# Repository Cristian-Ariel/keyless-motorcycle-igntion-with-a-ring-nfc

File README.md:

# Keyless Motorcycle Ignition System with a Ring (NFC)

The purpose of the system is to enable the ignition of a motorcycle without the use of a physical key, by utilizing an NFC tag (Near Field Communication). A few key features of the system include:
- Zero current consumption when the motorcycle is off, preventing battery discharge.
- The ability to store up to 128 different tags in memory, which are used as keys.
- Access to "Modes" such as Save/Delete Tag Mode and Erase All Tags Mode to prevent unauthorized use.
- A modular hardware design for prototyping and upgrades to accommodate different motorcycle makes and models.

## How do I build one?
Please watch the video on [Youtube](https://youtu.be/Ip3jwV7dnoM) or [Odysee](https://odysee.com/@AsyssComplex:1/keyless.motorcycle.ignition.with.ring:4?r=8kbGTNhCZ6iqTXnwzbdhoQCgzBPm1UvK).
Lastly, make sure to read [the documentation](https://drive.google.com/file/d/1D22VbdVqOc0YWlI75PouFQuNAUfmh6G7/view?usp=sharing). There you will find the materials and tools to build the system as well as several sections where we discuss the working principles of the system more in detail. The rest of the files, code, PCB files, 3D files are located in this repository.

## How do I contribute?
In the second page of the documentation, there is a brief description of how you can do it. Since the whole system is an ongoing project, I will edit this page and the description of the videos for future updates. Don't forget that you can also share your thoughts on the comment section of the videos.

## Enjoy!

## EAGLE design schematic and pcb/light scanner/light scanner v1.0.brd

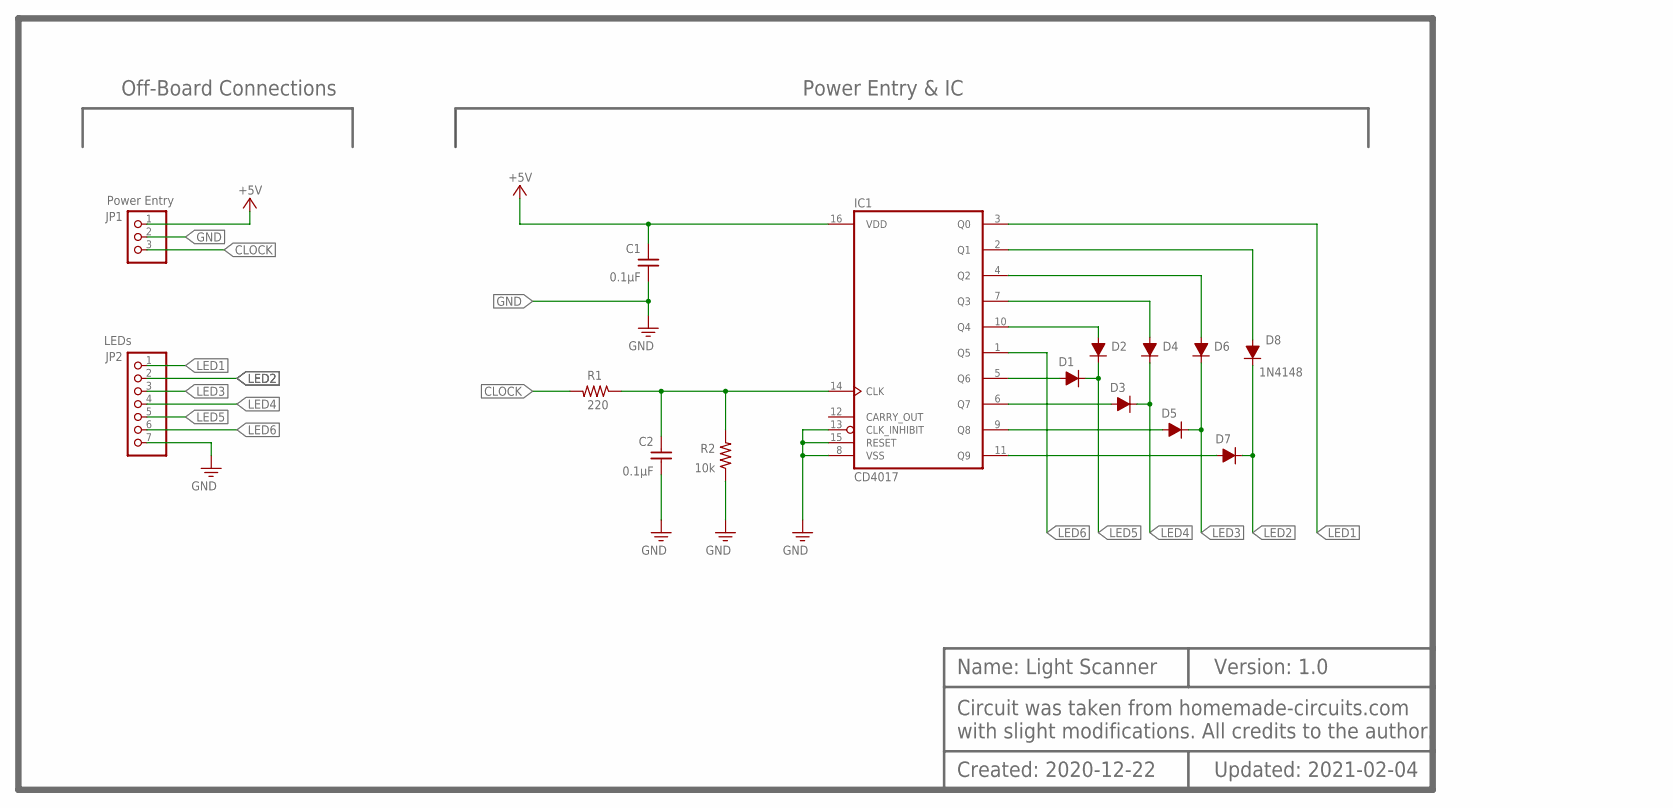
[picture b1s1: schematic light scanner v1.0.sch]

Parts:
C1, C2: 0.1µF; C_H5
D1, D2, D3, D4, D5, D6, D7: D_1N4148; DO35-7A
D8: 1N4148; DO35-7A
IC1: CD4017; DIP16
JP1: Power Entry; 1X03
JP2: LEDs; 1X07
R1: 220; R_THM
R2: 10k; R_THM

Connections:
+5V: C1.1, IC1.16 (VDD), JP1.1
CLOCK: JP1.3, R1.2
GND: C1.2, C2.2, IC1.8 (VSS), IC1.13 (CLK_INHIBIT), IC1.15 (RESET), JP1.2, JP2.7, R2.1
LED1: IC1.3 (Q0), JP2.1
LED2: D7.C, D8.C, JP2.2
LED3: D5.C, D6.C, JP2.3
LED4: D3.C, D4.C, JP2.4
LED5: D1.C, D2.C, JP2.5
LED6: IC1.1 (Q5), JP2.6
unnamed: C2.1, IC1.14 (CLK), R1.1, R2.2
unnamed: D1.A, IC1.5 (Q6)
unnamed: D2.A, IC1.10 (Q4)
unnamed: D3.A, IC1.6 (Q7)
unnamed: D4.A, IC1.7 (Q3)
unnamed: D5.A, IC1.9 (Q8)
unnamed: D6.A, IC1.4 (Q2)
unnamed: D7.A, IC1.11 (Q9)
unnamed: D8.A, IC1.2 (Q1)

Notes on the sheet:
Power Entry & IC
Off-Board Connections
Name: Light Scanner
Circuit was taken from homemade-circuits.com with slight modifications. All credits to the author.
Created: 2020-12-22
Updated: 2021-02-04
Version: 1.0

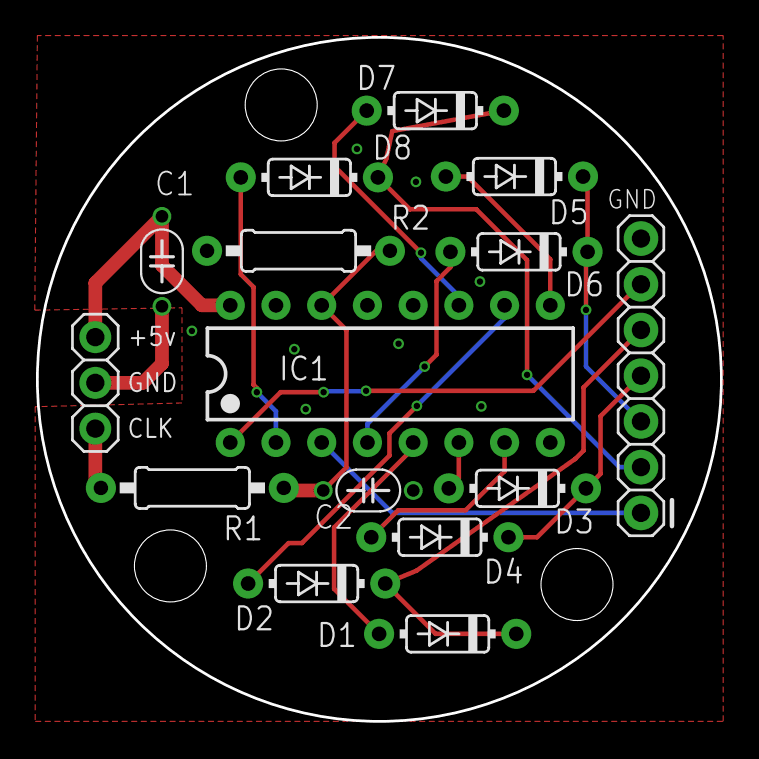
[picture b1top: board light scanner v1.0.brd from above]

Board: 2 copper layers, 38.0 x 38.0 mm, 16 parts (1 on the bottom side), 18 nets.

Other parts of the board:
U$2: ASSYS_COMP_LOGO_V6

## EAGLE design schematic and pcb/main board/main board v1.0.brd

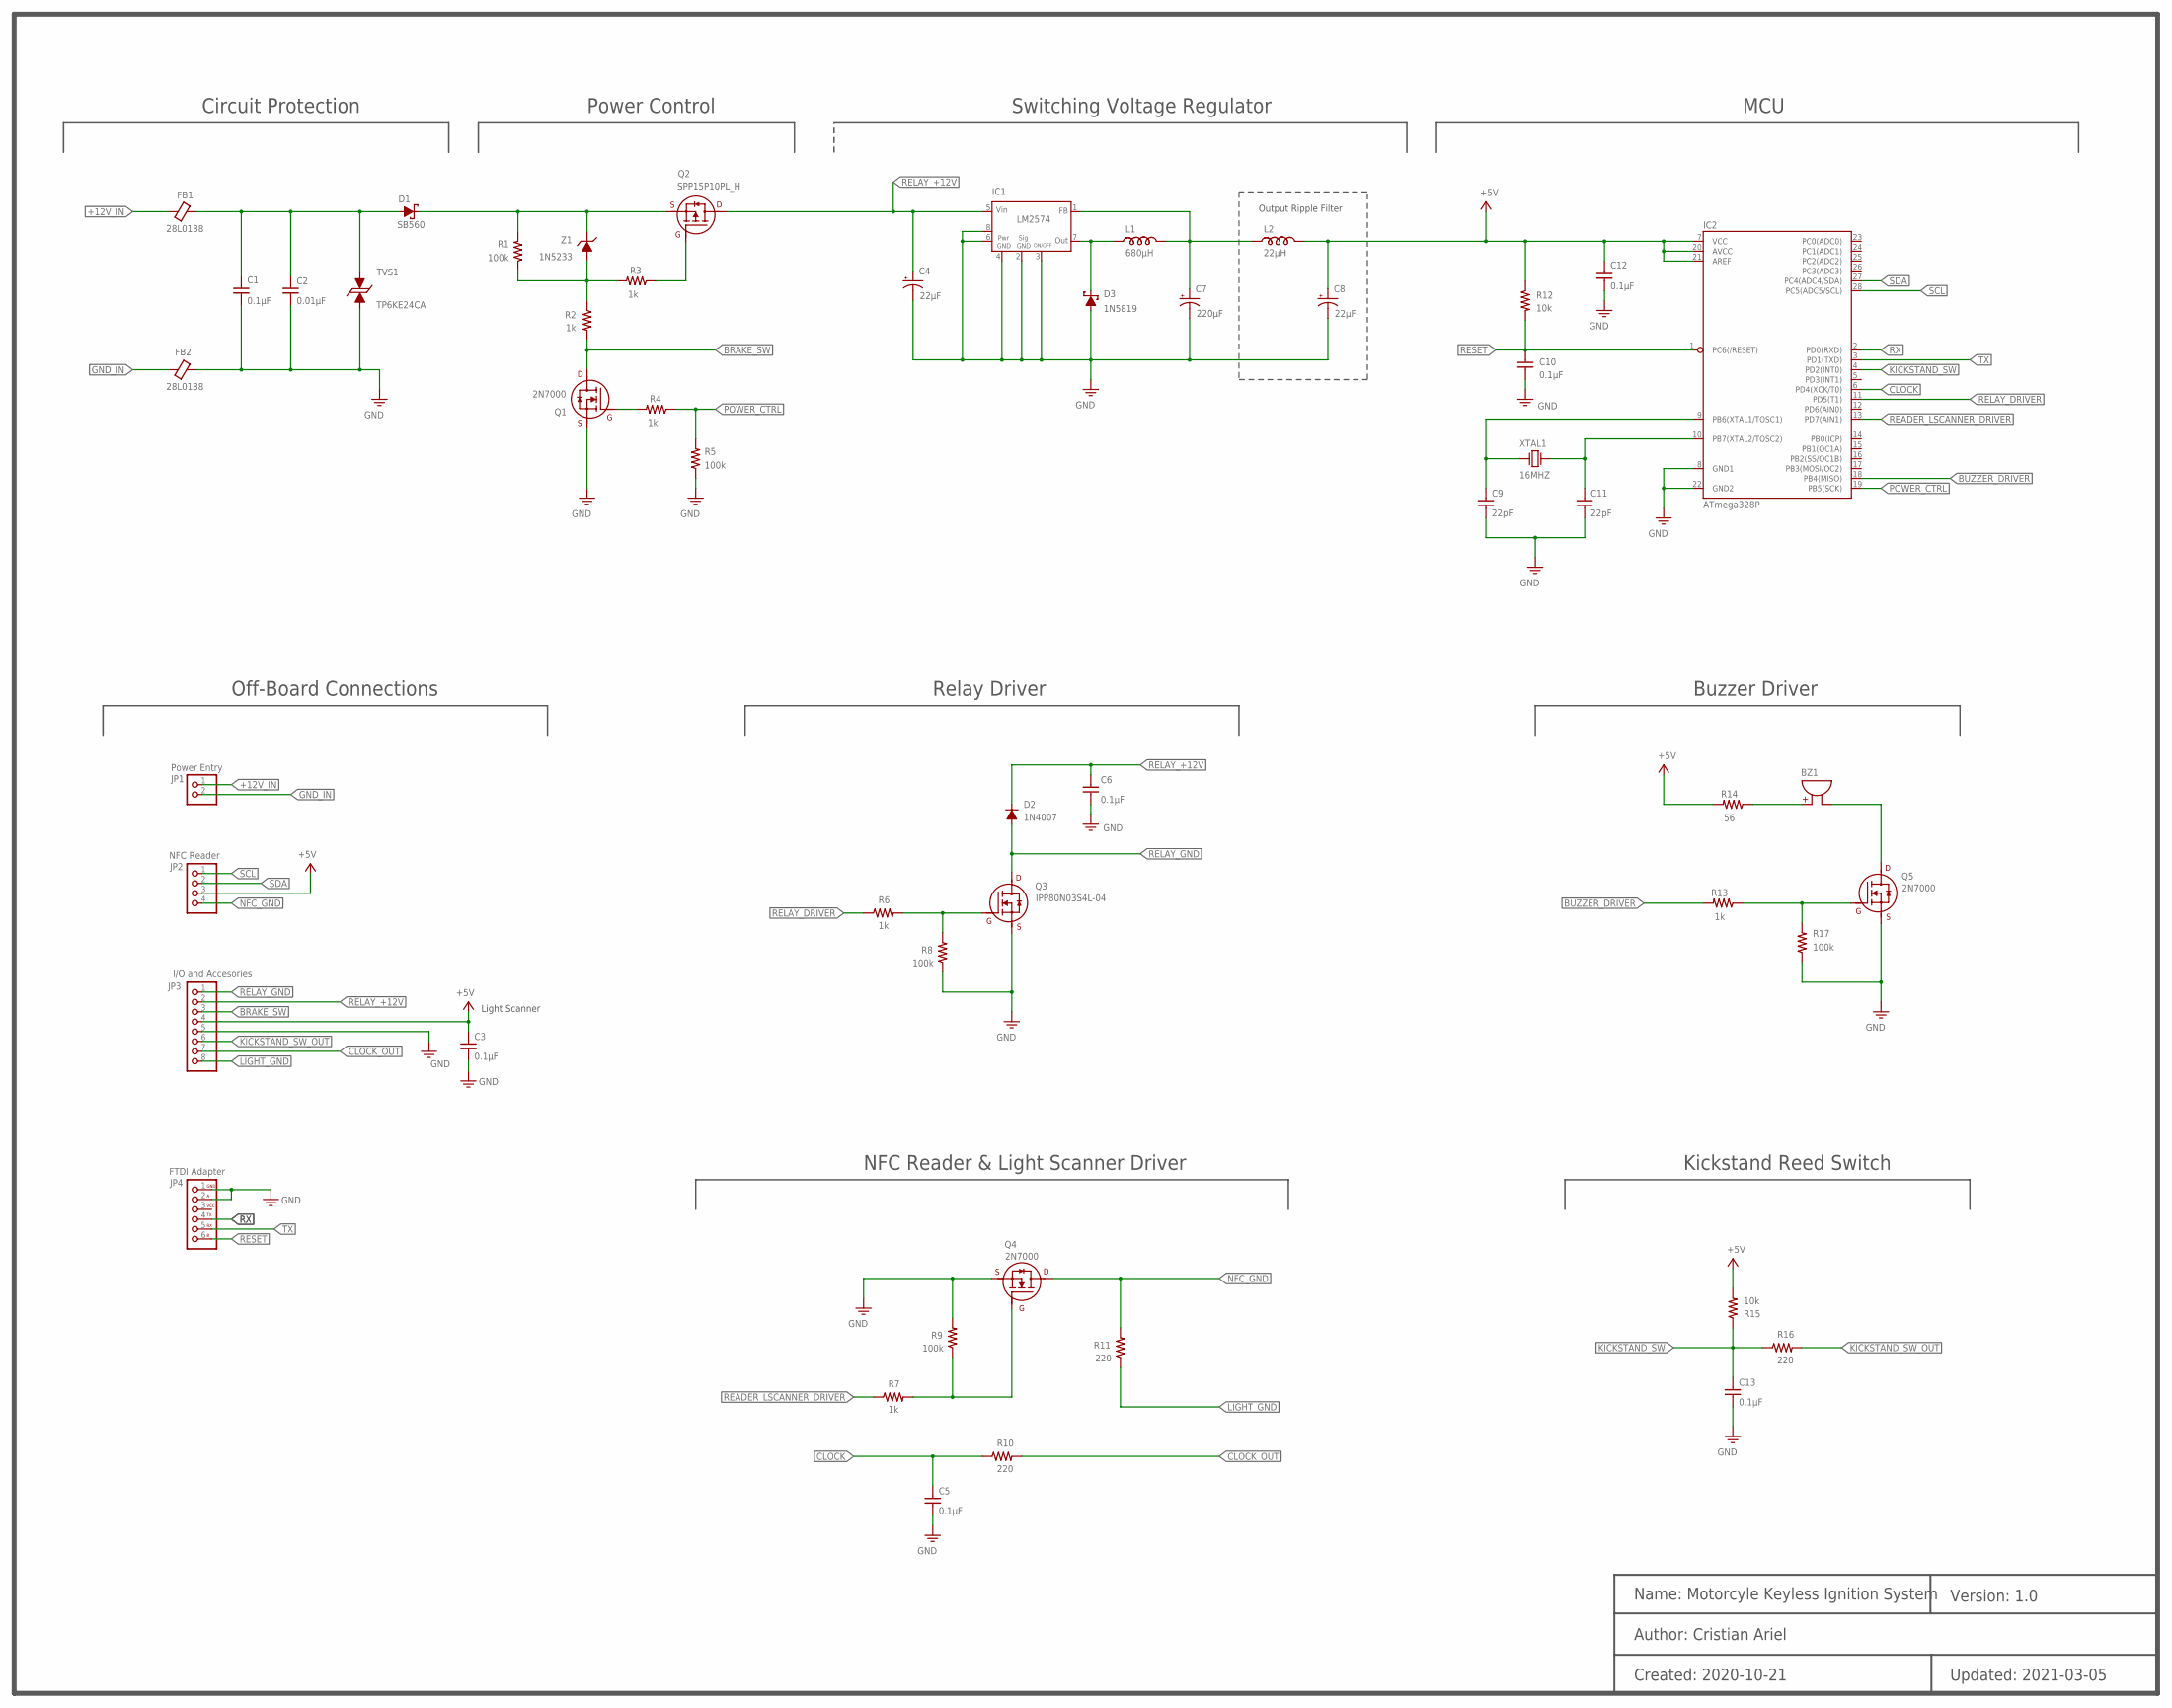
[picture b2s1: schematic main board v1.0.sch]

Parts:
BZ1: BUZZER_254-EMB15-RO; BUZZER-12
C1, C3, C5, C6, C10, C12, C13: 0.1µF; C_H5
C2: 0.01µF; C_H5
C4, C8: 22µF; C_UBT_8
C7: 220µF; C_UBT_10
C9, C11: 22pF; C_H5
D1: SB560; DO-201AD
D2: 1N4007; DO-41_(DO-204AL)
D3: 1N5819; DO-204AL_(DO-41)
FB1, FB2: 28L0138; FB-5.23
IC1: LM2574; DIL08
IC2: ATmega328P; DIP28
JP1: Power Entry; 1X021
JP2: NFC Reader; KK254_1X4
JP3: I/O and Accesories; 1X08
JP4: FTDI Adapter; 1X06_FTDI
L1: 680µH; PE-526
L2: 22µH; LTF-D
Q1, Q4, Q5: 2N7000; TO-92
Q2: SPP15P10PL_H; TO220
Q3: IPP80N03S4L-04; TO220
R1, R5, R8, R9, R17: 100k; R_THM
R2, R3, R4, R6, R7, R13: 1k; R_THM
R10, R11, R16: 220; R_THM
R12, R15: 10k; R_THM
R14: 56; R_THM
TVS1: TP6KE24CA; DO-204AC_(DO-15)
XTAL1: 16MHZ; HC-49USX
Z1: 1N5233; DO35-7A_ZENER

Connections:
+5V: C3.1, C8.+, C12.1, IC2.7 (VCC), IC2.20 (AVCC), IC2.21 (AREF), JP2.3, JP3.4, L2.1 (END), R12.1, R14.2, R15.2
+12V_IN: FB1.1, JP1.1
BRAKE_SW: JP3.3, Q1.3 (D), R2.2
BUZZER_DRIVER: IC2.18 (PB4(MISO)), R13.2
CLOCK: C5.1, IC2.6 (PD4(XCK/T0)), R10.1
CLOCK_OUT: JP3.7, R10.2
GND: C1.2, C2.2, C3.2, C4.-, C5.2, C6.2, C7.-, C8.-, C9.2, C10.2, C11.2, C12.2, C13.2, D3.A, FB2.2, IC1.2 (SIG_GND), IC1.3 (ON/OFF), IC1.4 (PWR_GND), IC1.6, IC1.8, IC2.8 (GND1), IC2.22 (GND2), JP3.5, JP4.1, JP4.2, Q1.1 (S), Q3.3 (S), Q4.1 (S), Q5.1 (S), R5.1, R8.1, R9.2, R17.1, TVS1.2
GND_IN: FB2.1, JP1.2
KICKSTAND_SW: C13.1, IC2.4 (PD2(INT0)), R15.1, R16.1
KICKSTAND_SW_OUT: JP3.6, R16.2
LIGHT_GND: JP3.8, R11.1
unnamed: BZ1.+, R14.1
unnamed: Q1.2 (G), R4.2
unnamed: D1.C, Q2.3 (S), R1.2, Z1.C
unnamed: Q2.1 (G), R3.1
unnamed: R1.1, R2.1, R3.2, Z1.A
unnamed: C9.1, IC2.9 (PB6(XTAL1/TOSC1)), XTAL1.1
unnamed: Q5.2 (G), R13.1, R17.2
unnamed: D3.C, IC1.7 (OUT), L1.1 (START)
unnamed: C7.+, IC1.1 (FB), L1.2 (END), L2.2 (START)
unnamed: C11.1, IC2.10 (PB7(XTAL2/TOSC2)), XTAL1.2
unnamed: Q3.1 (G), R6.2, R8.2
unnamed: Q4.2 (G), R7.2, R9.1
unnamed: BZ1.-, Q5.3 (D)
unnamed: C1.1, C2.1, D1.A, FB1.2, TVS1.1
NFC_GND: JP2.4, Q4.3 (D), R11.2
POWER_CTRL: IC2.19 (PB5(SCK)), R4.1, R5.2
READER_LSCANNER_DRIVER: IC2.13 (PD7(AIN1)), R7.1
RELAY_+12V: C4.+, C6.1, D2.C, IC1.5 (VIN), JP3.2, Q2.2 (D)
RELAY_DRIVER: IC2.11 (PD5(T1)), R6.1
RELAY_GND: D2.A, JP3.1, Q3.2 (D)
RESET: C10.1, IC2.1 (PC6(/RESET)), JP4.6, R12.2
RX: IC2.2 (PD0(RXD)), JP4.4
SCL: IC2.28 (PC5(ADC5/SCL)), JP2.1
SDA: IC2.27 (PC4(ADC4/SDA)), JP2.2
TX: IC2.3 (PD1(TXD)), JP4.5

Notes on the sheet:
Power Control
Circuit Protection
Switching Voltage Regulator
MCU
Off-Board Connections
Relay Driver
Buzzer Driver
NFC Reader & Light Scanner Driver
Output Ripple Filter
Kickstand Reed Switch
Name: Motorcyle Keyless Ignition System
Author: Cristian Ariel
Version: 1.0
Created: 2020-10-21
Updated: 2021-03-05
Light Scanner

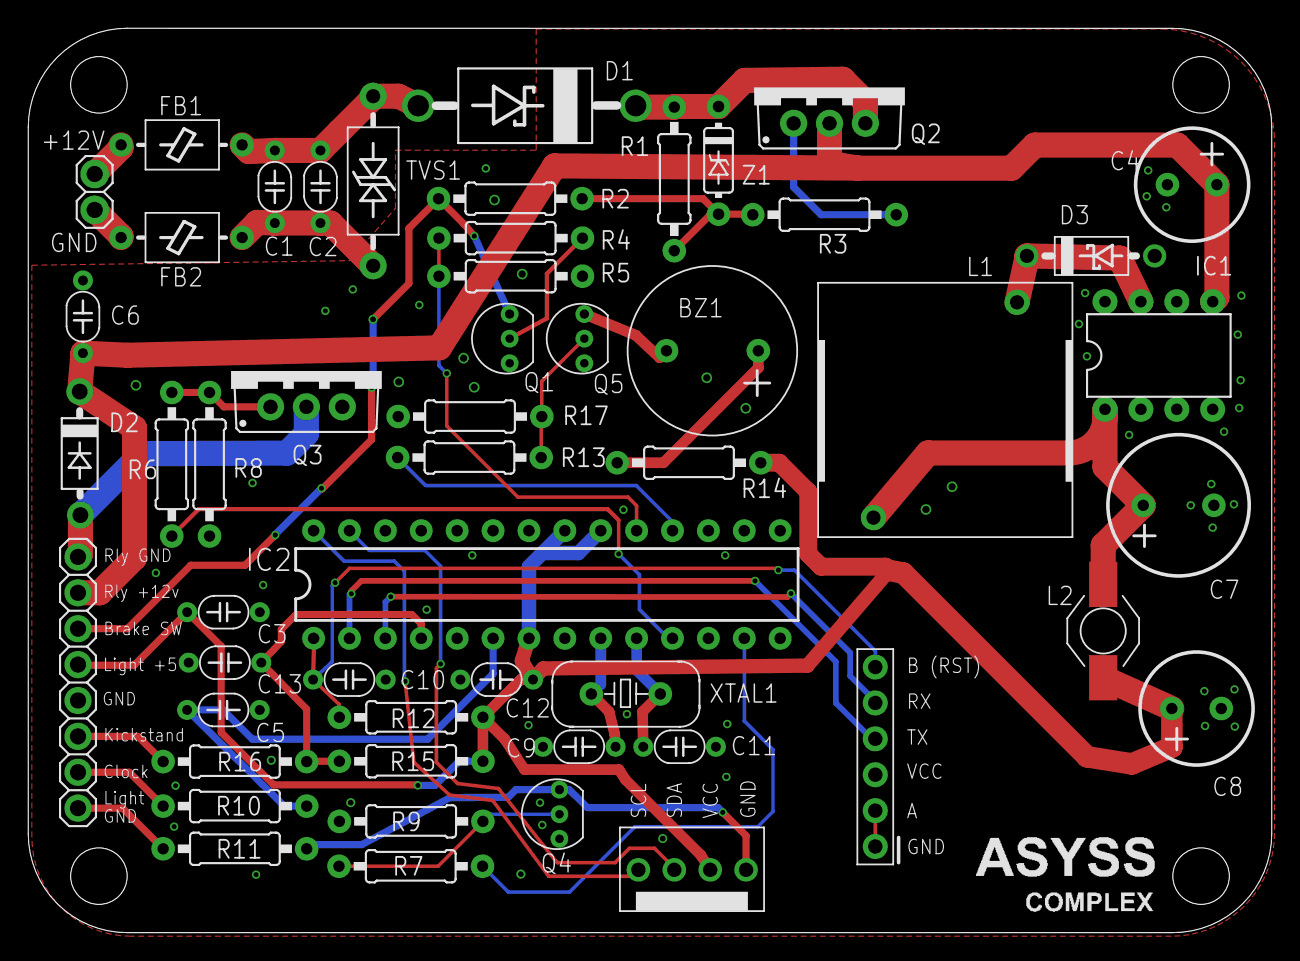
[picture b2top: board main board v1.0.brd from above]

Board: 2 copper layers, 88.0 x 64.0 mm, 54 parts (1 on the bottom side), 36 nets.

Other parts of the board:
U$1: ASSYS_COMP_LOGO_V5
U$2: ASSYS_COMP_LOGO_V6
